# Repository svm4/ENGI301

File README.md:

<h1> ENGI301 </h1>
Repository for ENGI301 course work

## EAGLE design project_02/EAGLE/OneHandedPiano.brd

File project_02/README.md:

<h1> One-Handed Piano PCB Design </h1>
<h2> Project Overview </h2>
The one-handed piano project combines my passion for music and memorization games. By memorizing a given sequence in which lights are illuminated, users will be able to play "Jingle Bells" on the one-handed piano. For this project, I created a printed circuit board (PCB) for my one-handed piano prototype. My Hackster.io page documents more information about the one-handed piano prototype and is linked here: https://www.hackster.io/svm4/pocketbeagle-one-handed-piano-06330d
<h2> Contents of this Project </h2>
First, I created a project proposal with a mechanical block diagram, as seen in the docs/ folder. Then, I used EAGLE to create my library, schematics, and layout for the project. These files are in the EAGLE/ folder. Next, I took screenshots of my four board layers and created Gerber manufacturing files. These can be found in the MFG/ folder. Assemblies of the top and bottom layer are also included. Additionally, there is a schematic PDF and Bill of Materials (both the CSV from EAGLE and the downloaded one from MacroFab) in the main project_02 directory. Finally, I created an account on MicroFab and generated price quotes for different board quantities with a 17 day lead time. 1 board costed $1,015.47, 10 boards costed $1,127.09, 100 boards costed $2,462.18, and 1000 boards costed $21,034.49.

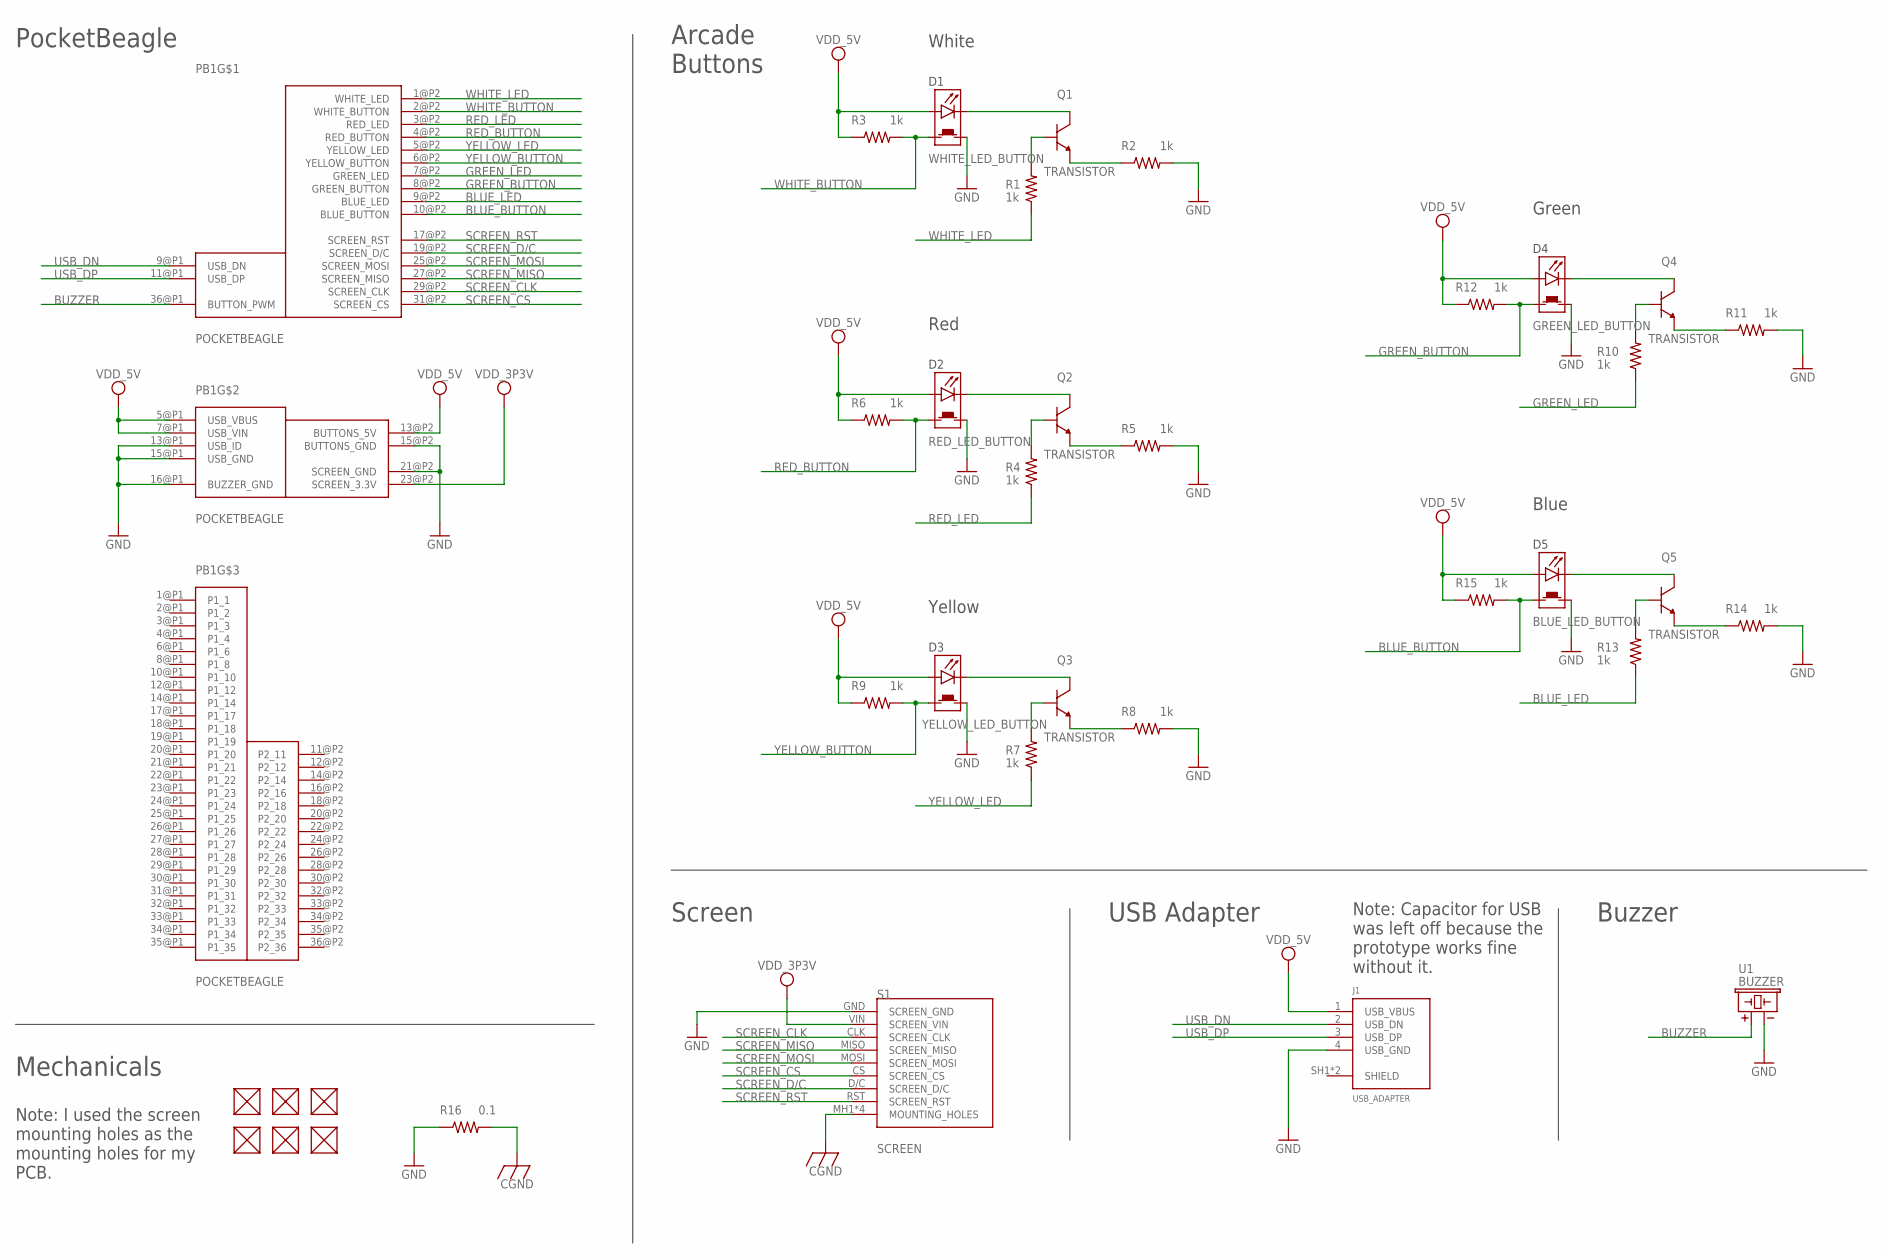
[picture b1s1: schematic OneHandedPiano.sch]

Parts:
D1: WHITE_LED_BUTTON; LED_BUTTON
D2: RED_LED_BUTTON; LED_BUTTON
D3: YELLOW_LED_BUTTON; LED_BUTTON
D4: GREEN_LED_BUTTON; LED_BUTTON
D5: BLUE_LED_BUTTON; LED_BUTTON
FUD1, FUD2, FUD3, FUD4, FUD5, FUD6: FIDUCIAL; FIDUCIAL_40MIL
J1: USB_ADAPTER
PB1: POCKETBEAGLE
Q1, Q2, Q3, Q4, Q5: TRANSISTOR
R1, R2, R3, R4, R5, R6, R7, R8, R9, R10, R11, R12, R13, R14, R15: 1k; R0603
R16: 0.1; R0805
S1: SCREEN
U1: BUZZER; BUZZER_6.5MM

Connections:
BLUE_BUTTON: D5.BUTTON1, PB1.10@P2 (BLUE_BUTTON), R15.2
BLUE_LED: PB1.9@P2 (BLUE_LED), R13.1
BUZZER: PB1.36@P1 (BUTTON_PWM), U1.+
CGND: R16.2, S1.MH1 (MOUNTING_HOLES), S1.MH2 (MOUNTING_HOLES), S1.MH3 (MOUNTING_HOLES), S1.MH4 (MOUNTING_HOLES)
GND: D1.BUTTON2, D2.BUTTON2, D3.BUTTON2, D4.BUTTON2, D5.BUTTON2, J1.4 (USB_GND), PB1.13@P1 (USB_ID), PB1.15@P1 (USB_GND), PB1.15@P2 (BUTTONS_GND), PB1.16@P1 (BUZZER_GND), PB1.21@P2 (SCREEN_GND), R2.2, R5.2, R8.2, R11.2, R14.2, R16.1, S1.GND (SCREEN_GND), U1.-
GREEN_BUTTON: D4.BUTTON1, PB1.8@P2 (GREEN_BUTTON), R12.2
GREEN_LED: PB1.7@P2 (GREEN_LED), R10.1
unnamed: D1.CATHODE, Q1.COLLECTOR
unnamed: Q1.BASE, R1.2
unnamed: Q1.EMITTER, R2.1
unnamed: D2.CATHODE, Q2.COLLECTOR
unnamed: Q2.BASE, R4.2
unnamed: Q2.EMITTER, R5.1
unnamed: D3.CATHODE, Q3.COLLECTOR
unnamed: Q3.BASE, R7.2
unnamed: Q3.EMITTER, R8.1
unnamed: D4.CATHODE, Q4.COLLECTOR
unnamed: Q4.BASE, R10.2
unnamed: Q4.EMITTER, R11.1
unnamed: D5.CATHODE, Q5.COLLECTOR
unnamed: Q5.BASE, R13.2
unnamed: Q5.EMITTER, R14.1
RED_BUTTON: D2.BUTTON1, PB1.4@P2 (RED_BUTTON), R6.2
RED_LED: PB1.3@P2 (RED_LED), R4.1
SCREEN_CLK: PB1.29@P2 (SCREEN_CLK), S1.CLK (SCREEN_CLK)
SCREEN_CS: PB1.31@P2 (SCREEN_CS), S1.CS (SCREEN_CS)
SCREEN_D/C: PB1.19@P2 (SCREEN_D/C), S1.D/C (SCREEN_D/C)
SCREEN_MISO: PB1.27@P2 (SCREEN_MISO), S1.MISO (SCREEN_MISO)
SCREEN_MOSI: PB1.25@P2 (SCREEN_MOSI), S1.MOSI (SCREEN_MOSI)
SCREEN_RST: PB1.17@P2 (SCREEN_RST), S1.RST (SCREEN_RST)
USB_DN: J1.2 (USB_DN), PB1.9@P1 (USB_DN)
USB_DP: J1.3 (USB_DP), PB1.11@P1 (USB_DP)
VDD_3P3V: PB1.23@P2 (SCREEN_3.3V), S1.VIN (SCREEN_VIN)
VDD_5V: D1.ANODE, D2.ANODE, D3.ANODE, D4.ANODE, D5.ANODE, J1.1 (USB_VBUS), PB1.5@P1 (USB_VBUS), PB1.7@P1 (USB_VIN), PB1.13@P2 (BUTTONS_5V), R3.1, R6.1, R9.1, R12.1, R15.1
WHITE_BUTTON: D1.BUTTON1, PB1.2@P2 (WHITE_BUTTON), R3.2
WHITE_LED: PB1.1@P2 (WHITE_LED), R1.1
YELLOW_BUTTON: D3.BUTTON1, PB1.6@P2 (YELLOW_BUTTON), R9.2
YELLOW_LED: PB1.5@P2 (YELLOW_LED), R7.1

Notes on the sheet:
PocketBeagle
Arcade Buttons
Screen
USB Adapter
Buzzer
White
Red
Yellow
Blue
Green
Note: Capacitor for USB was left off because the prototype works fine without it.
Mechanicals
Note: I used the screen mounting holes as the mounting holes for my PCB.

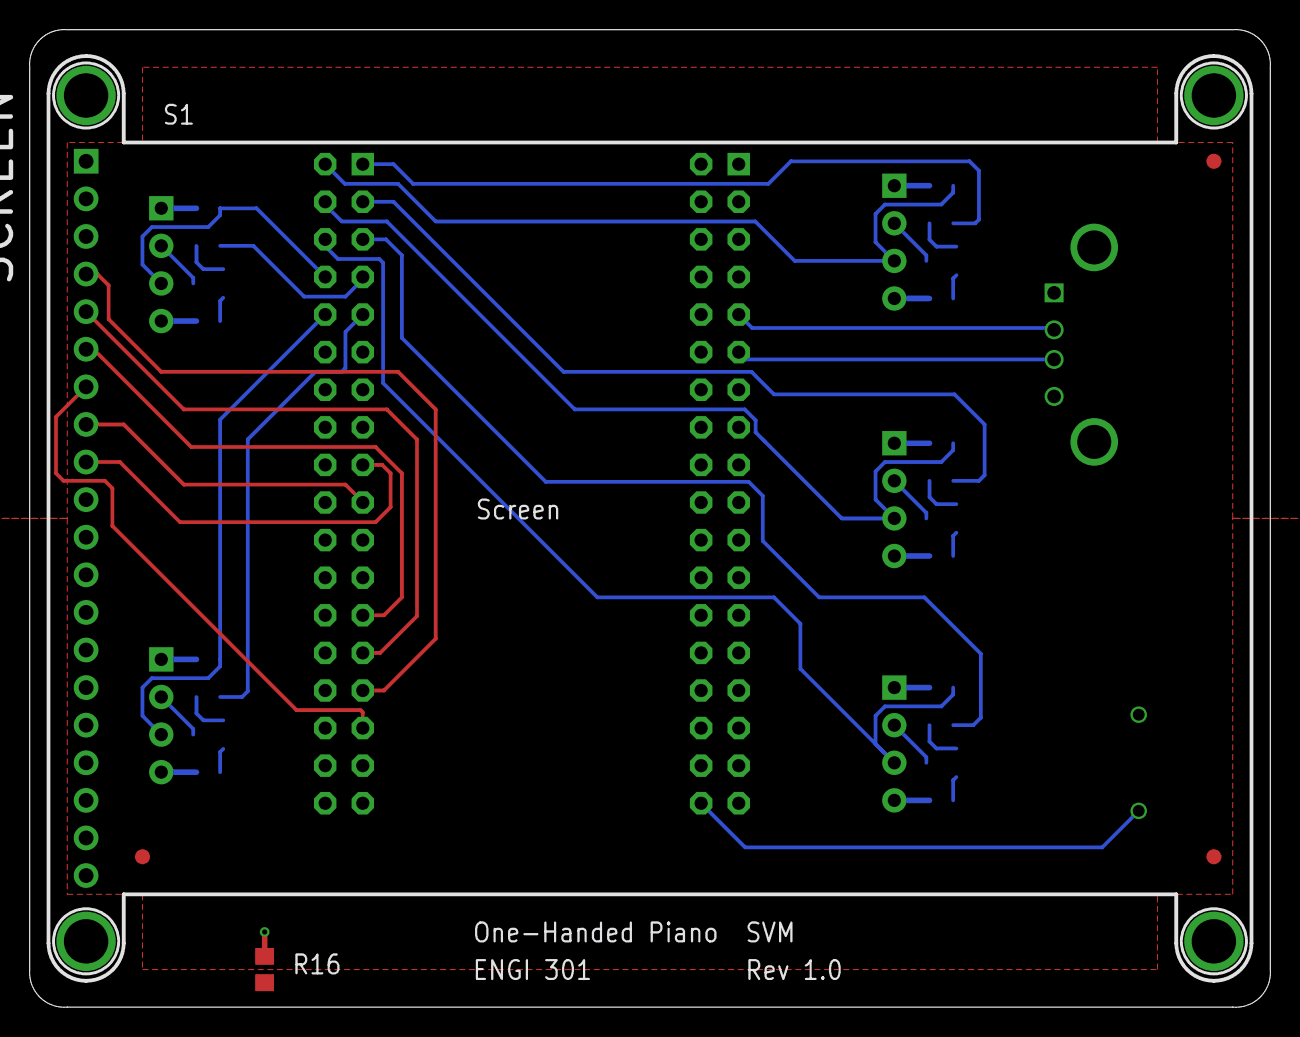
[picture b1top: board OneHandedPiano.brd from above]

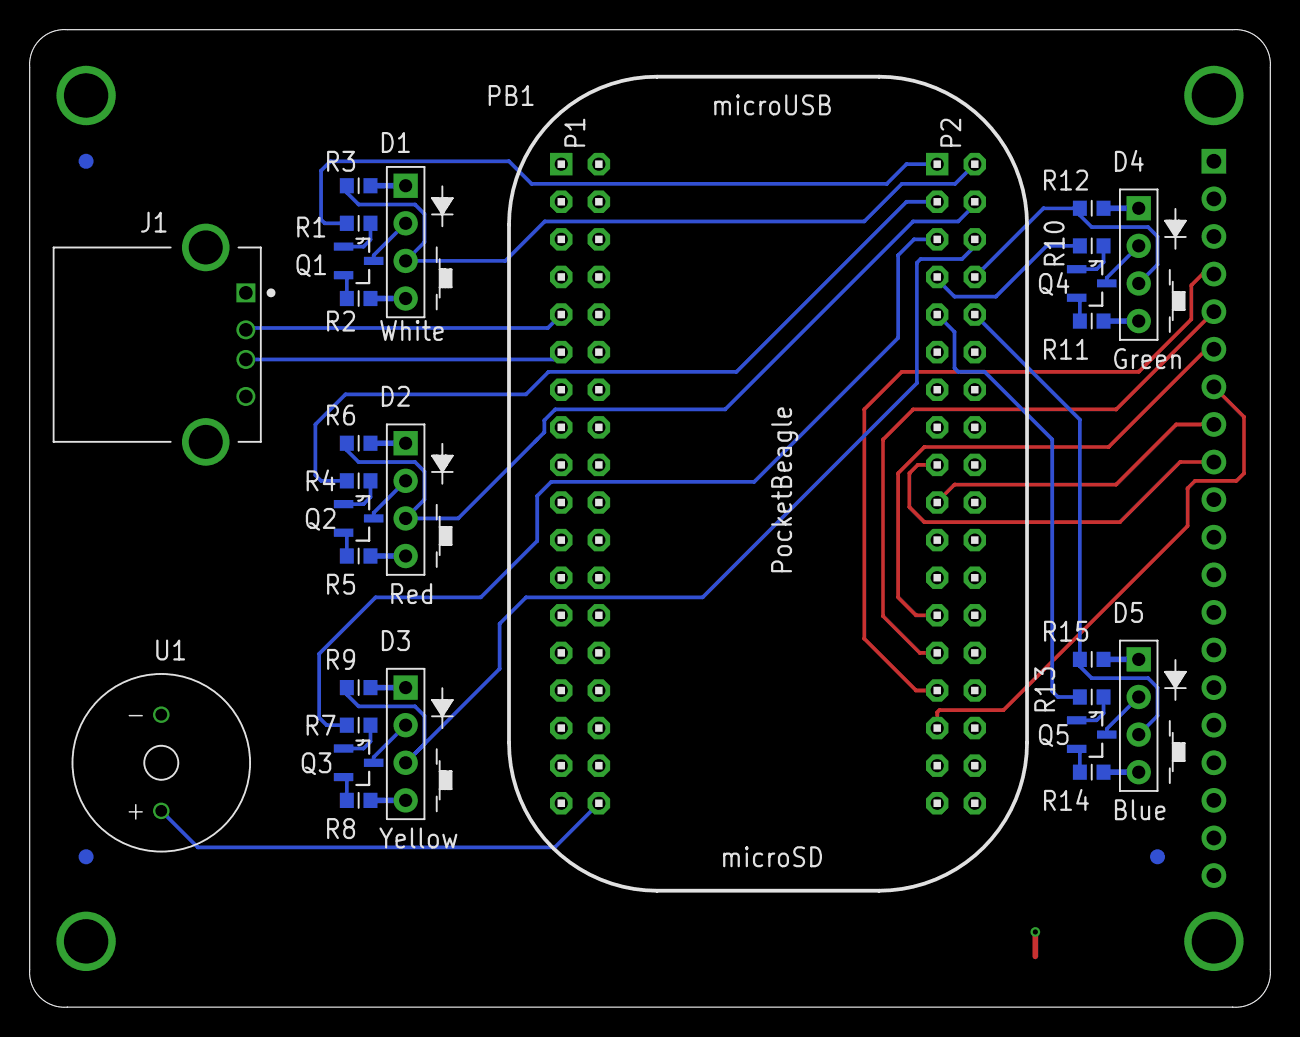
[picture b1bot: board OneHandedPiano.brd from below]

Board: 4 copper layers, 83.8 x 66.1 mm, 36 parts (31 on the bottom side), 38 nets.

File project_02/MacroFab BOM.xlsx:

Designator | Value | Footprint | Populate | MPN | Manufacturer
D1 | WHITE_LED_BUTTON | LED_BUTTON | 0
D2 | RED_LED_BUTTON | LED_BUTTON | 0
D3 | YELLOW_LED_BUTTON | LED_BUTTON | 0
D4 | GREEN_LED_BUTTON | LED_BUTTON | 0
D5 | BLUE_LED_BUTTON | LED_BUTTON | 0
J1 | USB_ADAPTER | USB_ADAPTER | 0
PB1 | POCKETBEAGLE | POCKETBEAGLE | 0 | POCKETBEAGLE | BeagleBoard
Q1 | TRANSISTOR | TRANSISTOR | 1 | MF-DSC-SOT233-MMBT3906 | MacroFab
Q2 | TRANSISTOR | TRANSISTOR | 1 | MF-DSC-SOT233-MMBT3906 | MacroFab
Q3 | TRANSISTOR | TRANSISTOR | 1 | MF-DSC-SOT233-MMBT3906 | MacroFab
Q4 | TRANSISTOR | TRANSISTOR | 1 | MF-DSC-SOT233-MMBT3906 | MacroFab
Q5 | TRANSISTOR | TRANSISTOR | 1 | MF-DSC-SOT233-MMBT3906 | MacroFab
R1 | 1k | R0603 | 1 | MF-RES-0603-1K | MacroFab
R10 | 1k | R0603 | 1 | MF-RES-0603-1K | MacroFab
R11 | 1k | R0603 | 1 | MF-RES-0603-1K | MacroFab
R12 | 1k | R0603 | 1 | MF-RES-0603-1K | MacroFab
R13 | 1k | R0603 | 1 | MF-RES-0603-1K | MacroFab
R14 | 1k | R0603 | 1 | MF-RES-0603-1K | MacroFab
R15 | 1k | R0603 | 1 | MF-RES-0603-1K | MacroFab
R16 | 0.1 | R0805 | 1 | ERJ-S6SFR10V | Panasonic
R2 | 1k | R0603 | 1 | MF-RES-0603-1K | MacroFab
R3 | 1k | R0603 | 1 | MF-RES-0603-1K | MacroFab
R4 | 1k | R0603 | 1 | MF-RES-0603-1K | MacroFab
R5 | 1k | R0603 | 1 | MF-RES-0603-1K | MacroFab
R6 | 1k | R0603 | 1 | MF-RES-0603-1K | MacroFab
R7 | 1k | R0603 | 1 | MF-RES-0603-1K | MacroFab
R8 | 1k | R0603 | 1 | MF-RES-0603-1K | MacroFab
R9 | 1k | R0603 | 1 | MF-RES-0603-1K | MacroFab
S1 | SCREEN | SCREEN | 0
U1 | BUZZER | BUZZER_6.5MM | 0
FUD1 | FIDUCIAL | FIDUCIAL_40MIL | 0
FUD2 | FIDUCIAL | FIDUCIAL_40MIL | 0
FUD3 | FIDUCIAL | FIDUCIAL_40MIL | 0
FUD4 | FIDUCIAL | FIDUCIAL_40MIL | 0
FUD5 | FIDUCIAL | FIDUCIAL_40MIL | 0
FUD6 | FIDUCIAL | FIDUCIAL_40MIL | 0

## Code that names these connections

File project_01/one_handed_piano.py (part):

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    button_list = None 
    Note_Map    = None
    
    def __init__(self, buzzer_pin="P1_36", white_button_pin="P2_2", white_led_pin="P2_1",
                    red_button_pin="P2_4", red_led_pin="P2_3", yellow_button_pin="P2_6",
                    yellow_led_pin="P2_5", green_button_pin="P2_8", green_led_pin="P2_7",
                    blue_button_pin="P2_10", blue_led_pin="P2_9", timeout=5, song_number=0):

        """ Initialize variables and set up display """

        self.buzzer   = buzzer.Buzzer(buzzer_pin)
        self.screen   = screen.SPI_Display()
        self.white    = color_button.ColorButton(white_button_pin, white_led_pin)
        self.red      = color_button.ColorButton(red_button_pin, red_led_pin)
        self.yellow   = color_button.ColorButton(yellow_button_pin, yellow_led_pin)
        self.green    = color_button.ColorButton(green_button_pin, green_led_pin)
        self.blue     = color_button.ColorButton(blue_button_pin, blue_led_pin)
        self.timeout  = timeout
        
        # Creates an array for the song based on the song index
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
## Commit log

2023-09-12 Updating README.md
2023-09-25 Committing simple calc
2023-09-28 Committing blink_USR3.py
2023-09-28 Commit of final blink_USR.py code
2023-09-28 Commit of final simple_calc.py code
2023-09-29 Commit of final button.py
2023-09-29 Commit of final blink_USR3 code
2023-10-02 Uploading updated project proposal and parts list
2023-10-13 Initial Draft of Software Block Diagram
2023-11-09 Button LEDs play song correctly
2023-11-09 Buzzer Class
2023-11-09 Screen Class
2023-11-09 Threaded Button Class
2023-11-09 LED Class
2023-11-09 Color Button Class
2023-11-09 Songs Class
2023-11-09 Configuring Pins
2023-11-09 Run File
2023-11-09 Added ability to push buttons to play songs
2023-11-10 Updated button_cleanup() function
2023-11-10 Working code minus sound
2023-11-10 Changed name of cleanup function
2023-11-10 Preliminary Sound Capability
2023-11-13 Finalized code without comments
2023-11-14 Screens used in program
2023-11-14 Buzzer Library
2023-11-14 LED Library
2023-11-14 LED Driver
2023-11-14 Buzzer Driver
2023-11-14 Screen Driver
2023-11-14 Threaded Buttton Driver
2023-11-14 Run Script
2023-11-14 Configure Pins
2023-11-14 Color Button Driver
2023-11-14 Songs Library
2023-11-14 One-Handed Piano Code (no comments)
2023-11-14 Screen Used in One-Handed Piano
2023-11-14 Color Button Library
2023-11-14 One-Handed Piano Code
2023-11-15 File to Test Speaker
2023-11-16 Updated Software Block Diagram
2023-12-11 Project Proposal
2023-12-11 One-Handed Piano Library
2023-12-11 One-Handed Piano Schematic
2023-12-11 One-Handed Piano Board
2023-12-11 Layer Screenshots
2023-12-11 Schematic PDF
2023-12-11 Bill of Materials
2023-12-11 Gerber Files
2023-12-12 Assembly Files
2023-12-12 Drill File
2023-12-12 Bill of Materials from MacroFab

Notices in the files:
project_01/one_handed_piano.py:
License:
Copyright 2023 - Shannon McGill
